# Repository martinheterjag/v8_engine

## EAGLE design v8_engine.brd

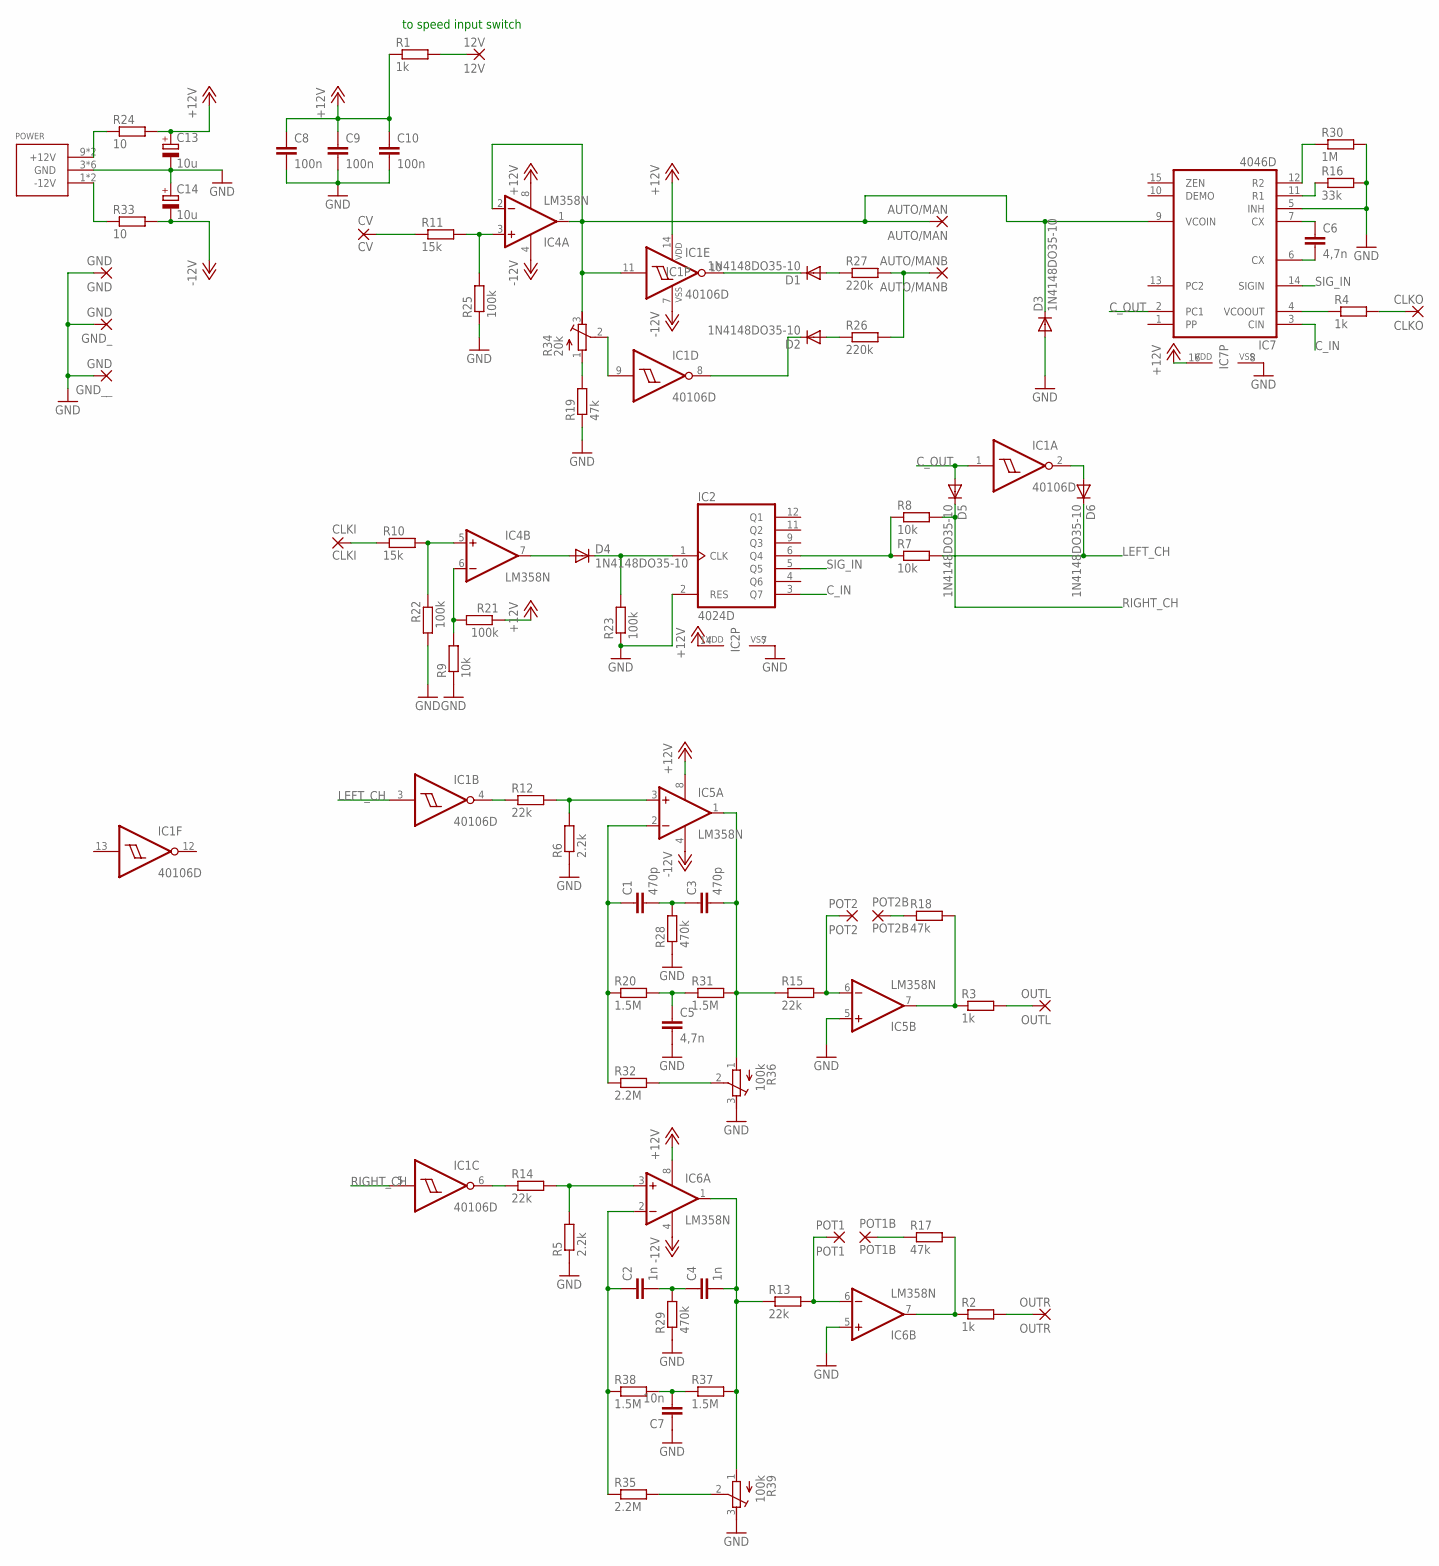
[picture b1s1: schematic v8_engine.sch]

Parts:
12V: 12V; 1,6/0,9
AUTO/MAN: AUTO/MAN; 1,6/0,9
AUTO/MANB: AUTO/MANB; 1,6/0,9
C1, C3: 470p; C050-025X075
C2, C4: 1n; C050-025X075
C5, C6: 4,7n; C050-025X075
C7: 10n; C050-025X075
C8, C9, C10: 100n; C050-025X075
C13, C14: 10u; E2,5-6
CLKI: CLKI; 1,6/0,9
CLKO: CLKO; 1,6/0,9
CV: CV; 1,6/0,9
D1, D2, D3, D4, D5, D6: 1N4148DO35-10; DO35-10
GND: GND; 1,6/0,9
GND_: GND; 1,6/0,9
GND__: GND; 1,6/0,9
IC1: 40106D; SO14
IC2: 4024D; SO14
IC4, IC5, IC6: LM358N; DIL08
IC7: 4046D; SO16
OUTL: OUTL; 1,6/0,9
OUTR: OUTR; 1,6/0,9
POT1: POT1; 1,6/0,9
POT1B: POT1B; 1,6/0,9
POT2: POT2; 1,6/0,9
POT2B: POT2B; 1,6/0,9
POWER: POWER_SIMPLE10; POWER_10
R1, R2, R3, R4: 1k; 0207/10
R5, R6: 2.2k; 0207/10
R7, R8, R9: 10k; 0207/10
R10, R11: 15k; 0207/10
R12, R13, R14, R15: 22k; 0207/10
R16: 33k; 0207/10
R17, R18, R19: 47k; 0207/10
R20, R31, R37, R38: 1.5M; 0207/10
R21, R22, R23, R25: 100k; 0207/10
R24, R33: 10; 0207/10
R26, R27: 220k; 0207/10
R28, R29: 470k; 0207/10
R30: 1M; 0207/10
R32, R35: 2.2M; 0207/10
R34: 20k; RTRIM3339P
R36, R39: 100k; RTRIM3339P

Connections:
+12V: C8.1, C9.1, C10.1, C13.+, IC1.14 (VDD), IC2.14 (VDD), IC4.8 (V+), IC5.8 (V+), IC6.8 (V+), IC7.16 (VDD), R1.1, R21.1, R24.2
-12V: C14.-, IC1.7 (VSS), IC4.4 (V-), IC5.4 (V-), IC6.4 (V-), R33.2
CLKO: CLKO.1, R4.2
C_IN: IC2.3 (Q7), IC7.3 (CIN)
C_OUT: D5.A, IC1.1 (I), IC7.2 (PC1)
GND: C5.2, C7.1, C8.2, C9.2, C10.2, C13.-, C14.+, D3.A, GND.1, GND_.1, GND__.1, IC2.2 (RES), IC2.7 (VSS), IC5.5 (+IN), IC6.5 (+IN), IC7.5 (INH), IC7.8 (VSS), POWER.3 (GND), POWER.4 (GND), POWER.5 (GND), POWER.6 (GND), POWER.7 (GND), POWER.8 (GND), R5.1, R6.1, R9.1, R16.2, R19.1, R22.2, R23.1, R25.1, R28.1, R29.1, R30.2, R36.3 (E), R39.3 (E)
LEFT_CH: D6.C, IC1.3 (I), R7.2
unnamed: IC7.4 (VCOOUT), R4.1
unnamed: D1.A, R27.1
unnamed: POWER.9 (+12V), POWER.10 (+12V), R24.1
unnamed: POWER.1 (-12V), POWER.2 (-12V), R33.1
unnamed: AUTO/MANB.1, R26.2, R27.2
unnamed: D2.C, IC1.8 (O)
unnamed: D2.A, R26.1
unnamed: D1.C, IC1.10 (O)
unnamed: IC1.9 (I), R34.2 (S)
unnamed: CLKI.1, R10.1
unnamed: R19.2, R34.1 (A)
unnamed: CV.1, R11.1
unnamed: IC4.3 (+IN), R11.2, R25.2
unnamed: IC4.5 (+IN), R10.2, R22.1
unnamed: C6.1, IC7.7 (CX)
unnamed: C6.2, IC7.6 (CX)
unnamed: IC7.11 (R1), R16.1
unnamed: IC7.12 (R2), R30.1
unnamed: D4.A, IC4.7 (OUT)
unnamed: D4.C, IC2.1 (CLK), R23.2
unnamed: IC2.6 (Q4), R7.1, R8.1
unnamed: IC4.6 (-IN), R9.2, R21.2
unnamed: IC1.4 (O), R12.1
unnamed: IC5.3 (+IN), R6.2, R12.2
unnamed: D6.A, IC1.2 (O)
unnamed: C1.1, IC5.2 (-IN), R20.1, R32.1
unnamed: R32.2, R36.2 (S)
unnamed: C3.2, IC5.1 (OUT), R15.1, R31.2, R36.1 (A)
unnamed: C5.1, R20.2, R31.1
unnamed: C1.2, C3.1, R28.2
unnamed: IC5.6 (-IN), POT2.1, R15.2
unnamed: IC5.7 (OUT), R3.1, R18.2
unnamed: POT2B.1, R18.1
unnamed: OUTL.1, R3.2
unnamed: C2.2, C4.1, R29.2
unnamed: C2.1, IC6.2 (-IN), R35.1, R38.1
unnamed: C4.2, IC6.1 (OUT), R13.1, R37.2, R39.1 (A)
unnamed: C7.2, R37.1, R38.2
unnamed: 12V.1, R1.2
unnamed: IC1.6 (O), R14.1
unnamed: IC6.3 (+IN), R5.2, R14.2
unnamed: IC6.6 (-IN), POT1.1, R13.2
unnamed: OUTR.1, R2.2
unnamed: POT1B.1, R17.1
unnamed: IC6.7 (OUT), R2.1, R17.2
unnamed: R35.2, R39.2 (S)
unnamed: AUTO/MAN.1, D3.C, IC1.11 (I), IC4.1 (OUT), IC4.2 (-IN), IC7.9 (VCOIN), R34.3 (E)
RIGHT_CH: D5.C, IC1.5 (I), R8.2
SIG_IN: IC2.5 (Q5), IC7.14 (SIGIN)

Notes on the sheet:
to speed input switch

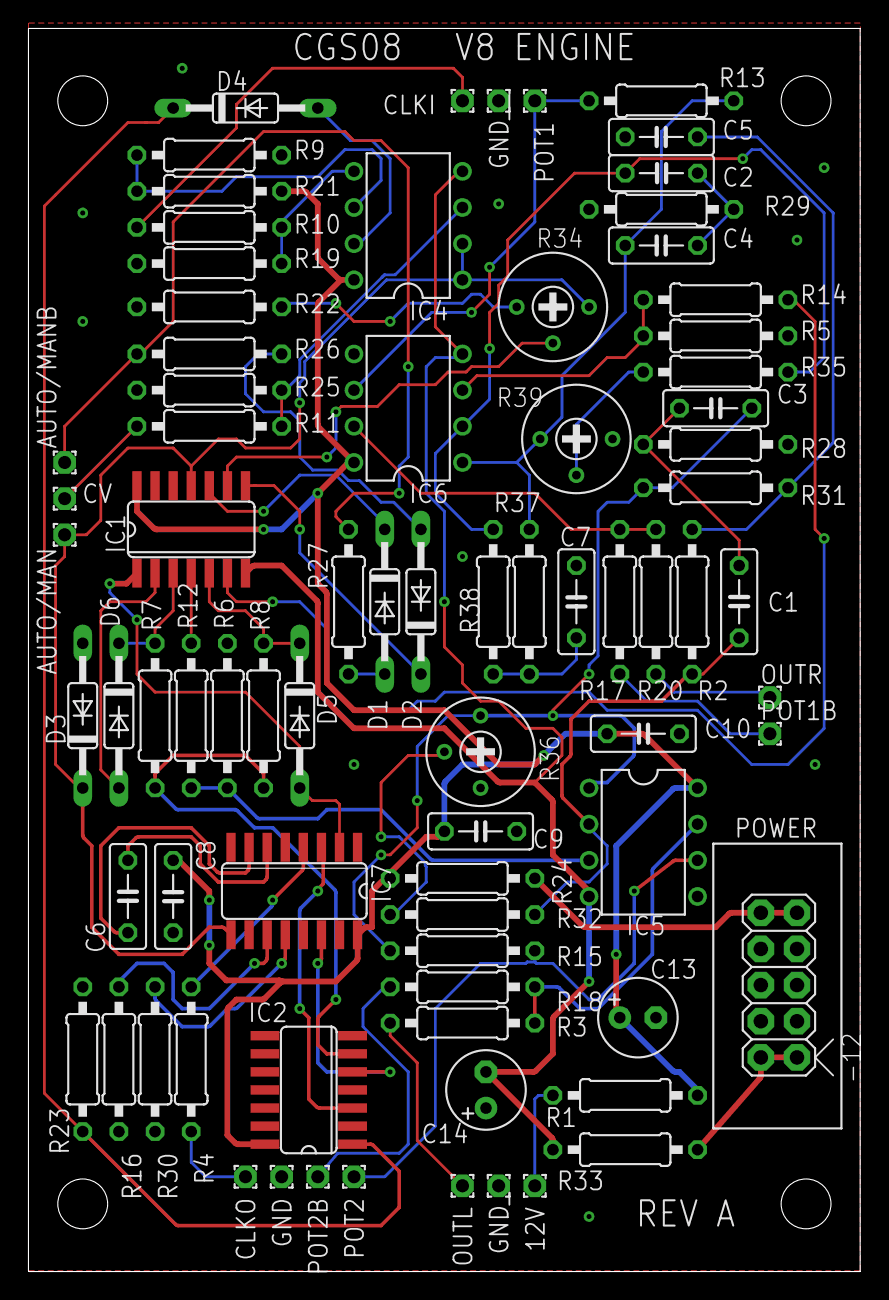
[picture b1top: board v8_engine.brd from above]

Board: 2 copper layers, 58.4 x 87.3 mm, 79 parts (0 on the bottom side), 56 nets.

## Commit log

2017-11-16 First commit - Draw schematic
    Copy v8 sim schematic from cgs.synth.net
2017-11-16 Rearrange all components on the PCB
    - Arrange components on pcb to make some kind of sense.
    - Change size of board and add screw holes for m3 screw.
    - Note that size/layout might not be final.
    - Invoke all ICs to connect them to +12V -12V and GND nets.
2017-11-22 Change big ICs from DIL to SO make board smaller and start routing
2017-12-18 Complete routing
2018-01-07 Clean up silk screen and fix issues
2018-01-07 Fix overlapping silk screen

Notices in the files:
v8_engine.brd:
Copyright 2018 by Martin Eriksson
